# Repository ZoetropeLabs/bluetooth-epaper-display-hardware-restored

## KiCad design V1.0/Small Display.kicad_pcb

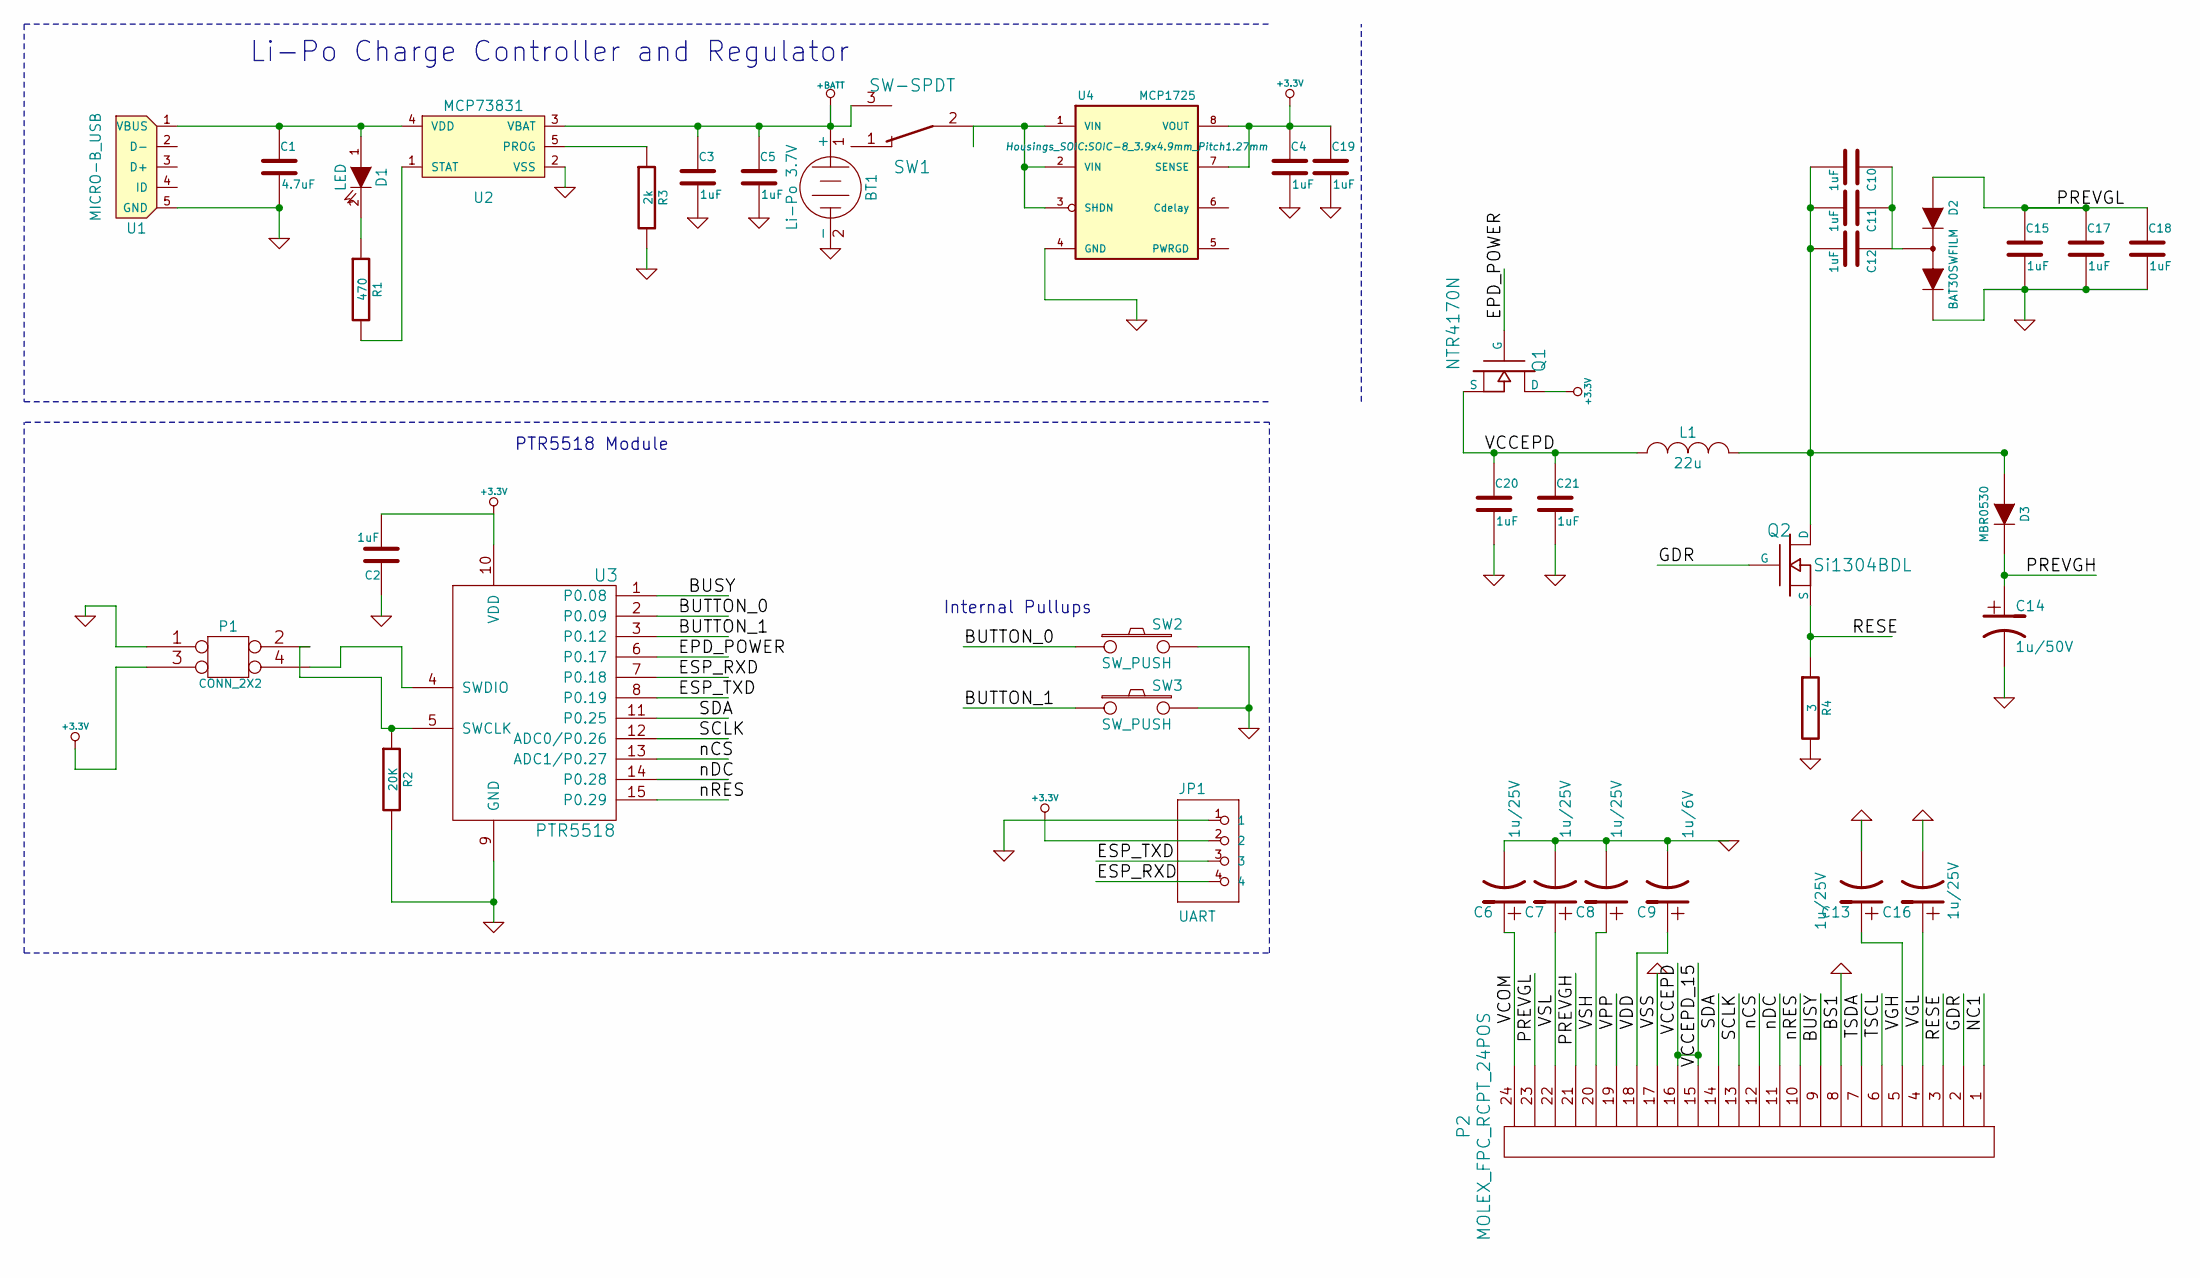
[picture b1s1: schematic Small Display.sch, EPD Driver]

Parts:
BT1: Li-Po 3.7V; Pin_Header_Straight_1x02
C1: 4.7uF; TantalC_SizeC_EIA-6032_Reflow
C2, C10, C11, C12, C15, C17, C18: 1uF; C_0603
C3, C4, C19, C20, C21: 1uF; TantalC_SizeC_EIA-6032_Reflow
C5: 1uF
C6, C7, C8, C13, C16: 1u/25V; C_0603
C9: 1u/6V; C_0603
C14: 1u/50V; C_0603
D1: LED; LED-0603
D2: BAT30SWFILM; SOT-323
D3: MBR0530; SOD-323
JP1: UART; Pin_Header_Straight_1x04
L1: 22u; R_1210_HandSoldering
P1: CONN_2X2; Pin_Header_Straight_2x02
P2: MOLEX_FPC_RCPT_24POS; MOLEX_FPC_RCPT_24POS_0_5MM
Q1: NTR4170N; SOT-23
Q2: Si1304BDL; SOT-323
R1: 470; R_0603
R2: 20K; R_0603
R3: 2k; R_0603
R4: 3; R_0603
SW1: SW-SPDT; SW_Micro_SPST
SW2, SW3: SW_PUSH; SW_M6_COMBO
U1: MICRO-B_USB; conn_usb_B_micro_smd
U2: MCP73831; SOT-23-5
U3: PTR5518
U4: MCP1725; SOIC-8_3.9x4.9mm_Pitch1.27mm

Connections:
+BATT: BT1.1 (+), C3.1, C5.1, SW1.3, U2.3 (VBAT)
/BUSY: P2.9, U3.1 (P0.08)
/BUTTON_0: SW2.1, U3.2 (P0.09)
/BUTTON_1: SW3.1, U3.3 (P0.12)
/EPD_POWER: Q1.1 (G), U3.6 (P0.17)
/ESP_RXD: JP1.4, U3.7 (P0.18)
/ESP_TXD: JP1.3, U3.8 (P0.19)
/GDR: P2.2, Q2.1 (G)
/NC1: P2.1
/PREVGH: C14.1, D3.2 (K), P2.21
/PREVGL: C15.1, C17.1, C18.1, D2.1 (A), P2.23
/RESE: P2.3, Q2.2 (S), R4.1
/SCLK: P2.13, U3.12 (ADC0/P0.26)
/SDA: P2.14, U3.11 (P0.25)
/TSCL: P2.6
/TSDA: P2.7
/VCCEPD: C20.1, C21.1, L1.1, P2.15, P2.16, Q1.2 (S)
/VCOM: C6.1, P2.24
/VDD: C9.1, P2.18
/VGH: C13.1, P2.5
/VGL: C16.1, P2.4
/VPP: P2.19
/VSH: C8.1, P2.20
/VSL: C7.1, P2.22
/nCS: P2.12, U3.13 (ADC1/P0.27)
/nDC: P2.11, U3.14 (P0.28)
/nRES: P2.10, U3.15 (P0.29)
unnamed: C1.1, D1.1 (A), U1.1 (VBUS), U2.4 (VDD)
unnamed: C10.1, C11.1, C12.1, D2.3 (Com)
unnamed: C10.2, C11.2, C12.2, D3.1 (A), L1.2, Q2.3 (D)
unnamed: D1.2 (K), R1.1
unnamed: P1.2, R2.1, U3.5 (SWCLK)
unnamed: P1.4, U3.4 (SWDIO)
unnamed: R1.2, U2.1 (STAT)
unnamed: R3.1, U2.5 (PROG)
unnamed: SW1.2, U4.1 (VIN), U4.2 (VIN), U4.3 (SHDN)

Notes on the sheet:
Li-Po Charge Controller and Regulator
PTR5518 Module
Internal Pullups

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
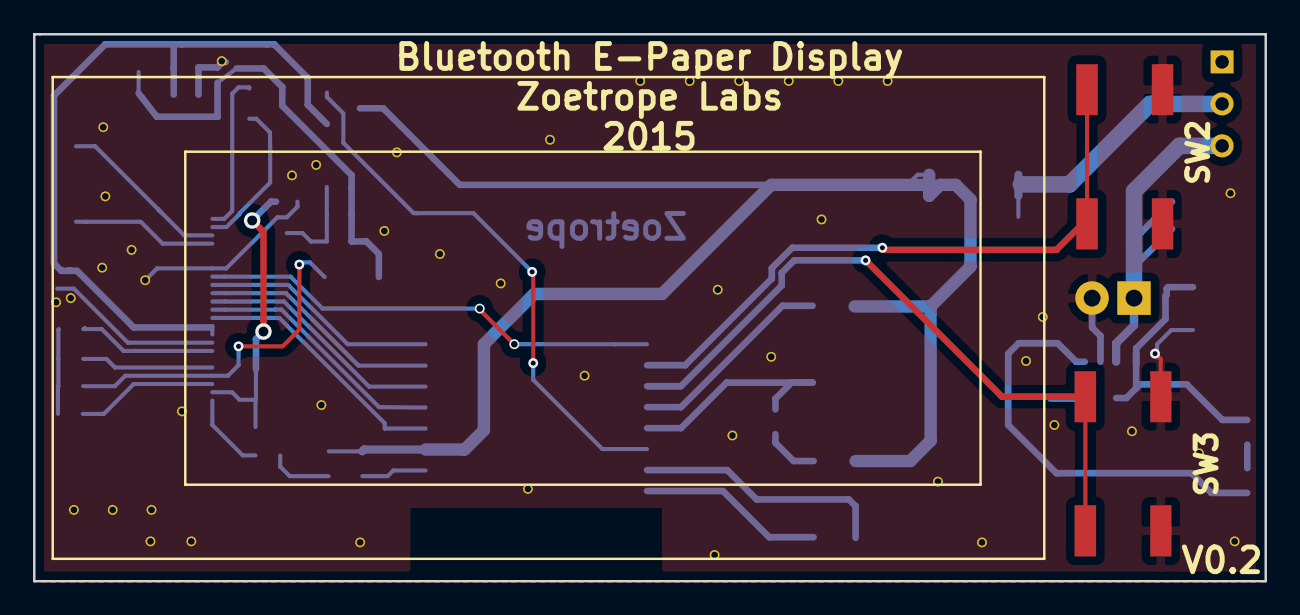
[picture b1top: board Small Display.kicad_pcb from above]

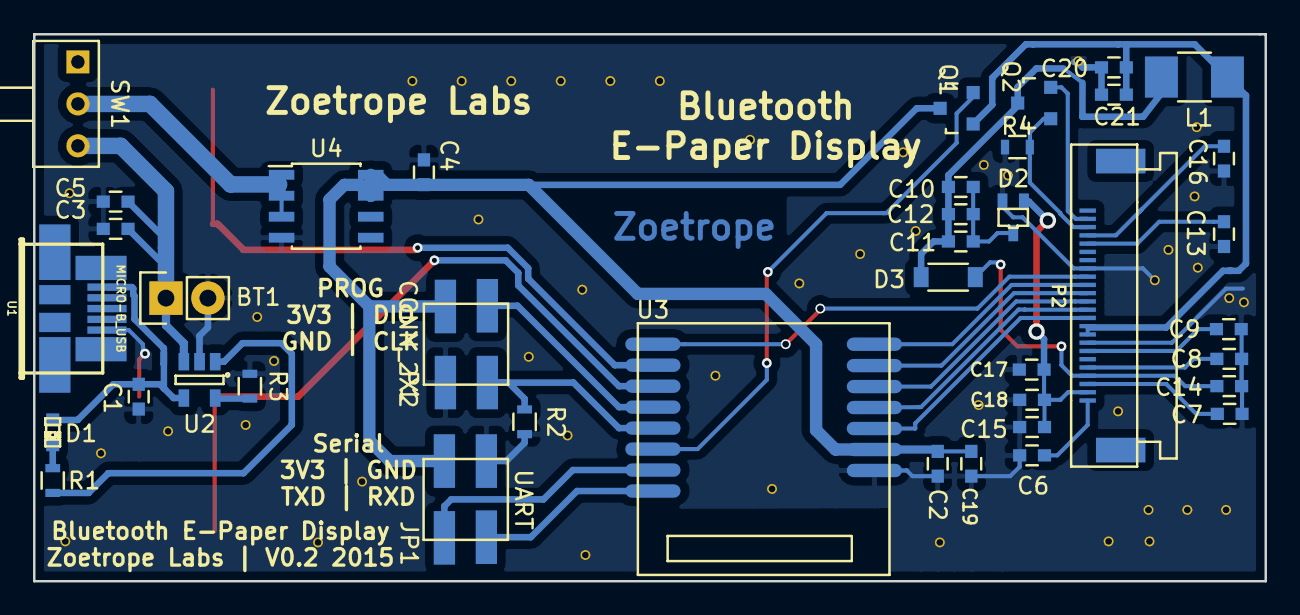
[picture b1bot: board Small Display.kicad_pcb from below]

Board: 2 copper layers, 74.6 x 33.1 mm, 42 parts (40 on the bottom side), 34 nets.

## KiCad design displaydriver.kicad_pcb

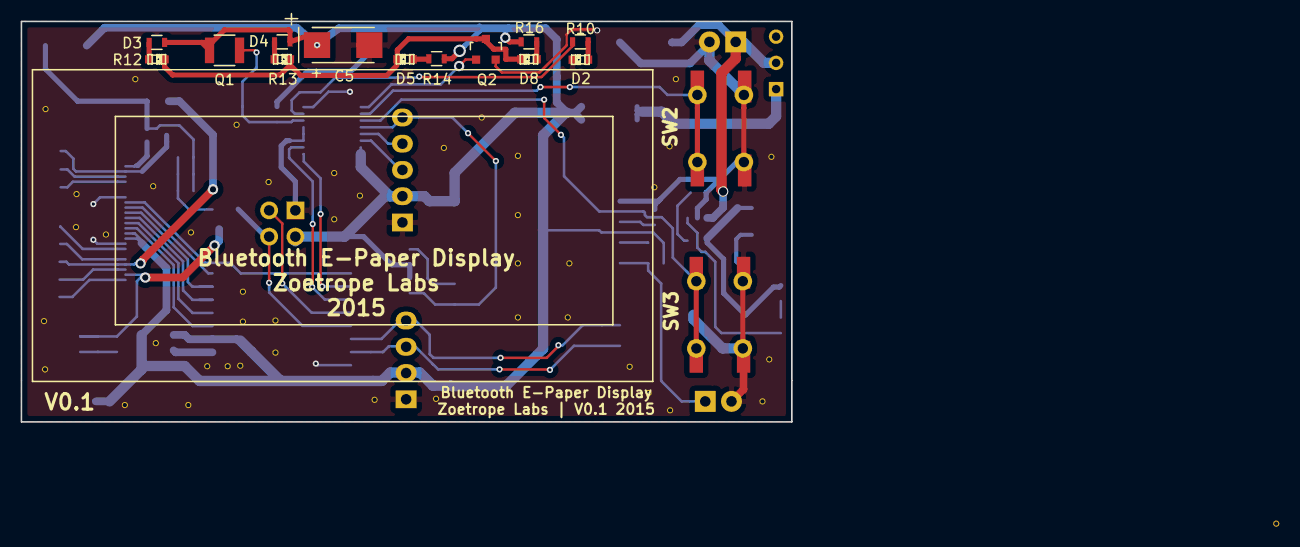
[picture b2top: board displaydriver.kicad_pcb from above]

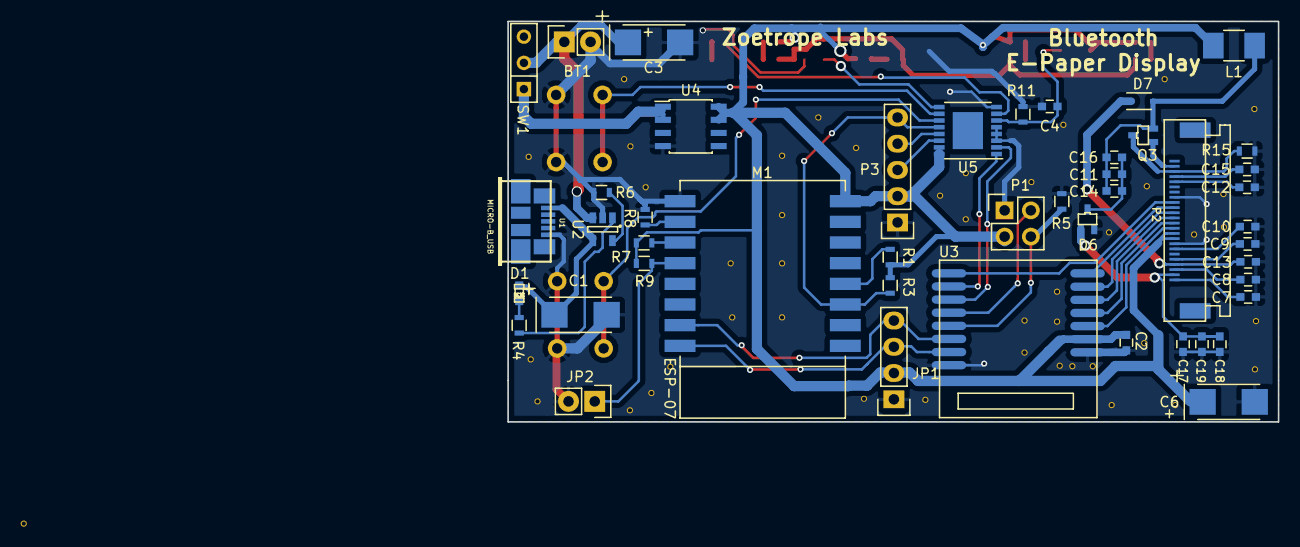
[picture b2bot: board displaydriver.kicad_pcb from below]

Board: 2 copper layers, 74.6 x 38.8 mm, 109 parts (46 on the bottom side), 50 nets.

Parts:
BT1: Li-Po 3.7V; Pin_Header_Straight_1x02
C1, C3, C5: 4.7uF; TantalC_SizeC_EIA-6032_Reflow
C2, C4: C; C_0603
C6: 4u7/6V; TantalC_SizeC_EIA-6032_Reflow
C7, C8, C9, C12, C15: 1u/25V; C_0603
C10: 1u/6V; C_0603
C11, C14, C16, C17, C18, C19: 1uF; C_0603
C13: 1u/50V; C_0603
D1, D2, D3, D4, D5, D8: LED; LED-0603
D6: BAT30SWFILM; SOT-323
D7: MBR0530; SOD-323
GND2, GND3, GND6, GND7, GND8, GND9, GND10, GND14, GND15, GND16, GND17, GND18, GND19, GND20, GND22, GND23, GND24, GND25, GND25#2, GND26, GND27, GND28, GND29, GND30, GND31, GND32, GND33, GND34, GND41, GND41#2, GND42, GND42#2, GND43, GND44, GND45, GND46, GND46#2, GND46#3, GND47, GND48, GND48#2, GND48#3, GND49, GND51, GND52, GND61, GND410, GND411: GND; VIA_0.6_0.4
JP1: UART; Pin_Header_Straight_1x04
JP2: JUMPER; Pin_Header_Straight_1x02
L1: 22u; R_1210_HandSoldering
M1: ESP-07
P1: CONN_2X2; Pin_Header_Straight_2x02
P2: MOLEX_FPC_RCPT_24POS; MOLEX_FPC_RCPT_24POS_0_5MM
P3: CONN_5; Pin_Header_Straight_1x05
Q1: PHOTO-TRANSISTOR-NPN; R_1210
Q2: NTR4170N; SOT-23
Q3: Si1304BDL; SOT-323
R1, R3, R7, R8, R9: 10K; R_0603
R4, R6, R10, R11, R12, R13, R14, R16: R; R_0603
R5: 20K; R_0603
R15: 3R; R_0603
SW1: SW-SPDT; SW_Micro_SPST
SW2, SW3: SW_PUSH; SW_M6_COMBO
U1: MICRO-B_USB; conn_usb_B_micro_smd
U2: MCP73831; SOT-23-5
U3: PTR5518
U4: MCP1725; SOIC-8_3.9x4.9mm_Pitch1.27mm
U5: PCA9557PWR; TSSOP-16-1EP_4.4x5mm_Pitch0.65mm

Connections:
+3.3V: C2.2, C5.1, C6.1, JP1.2, L1.1, M1.8, P1.3, P2.15, P2.16, P3.2, Q1.1, R1.1, R3.1, R7.2, R9.2, R12.1, R13.1, R14.1, R16.1, U3.10, U4.7, U4.8, U5.15, U5.16
+BATT: BT1.1, C3.1, SW1.2, U2.3
/BACKLIGHT: Q2.1, U5.9
/BUSY: P2.9, U3.1
/BUTTON_0: SW2.1, U5.10
/BUTTON_1: SW3.1, U5.11
/ESP_CH_PD: M1.3, P3.5, R3.2, U5.12
/ESP_RXD: JP1.4, M1.15, U3.6
/ESP_TXD: JP1.3, M1.16, U3.7
/GDR: P2.2, Q3.1
/IO_SCL: U3.2, U5.1
/IO_SDA: U3.3, U5.2
/NOTIF_LED: R10.2, U5.7
/PREVGH: C13.1, D7.2, P2.21
/PREVGL: C17.1, C18.1, C19.1, D6.1, P2.23
/RESE: P2.3, Q3.3, R15.1
/SCLK: P2.13, U3.12
/SDA: P2.14, U3.11
/VCOM: C7.1, P2.24
/VDD: C10.1, P2.18
/VGH: C12.1, P2.5
/VGL: C15.1, P2.4
/VSH: C9.1, P2.20
/VSL: C8.1, P2.22
/nCS: P2.12, U3.13
/nDC: P2.11, U3.14
/nRES: P2.10, U3.15
GND: BT1.2, C1.2, C2.1, C3.2, C4.2, C5.2, C6.2, C7.2, C8.2, C9.2, C10.2, C12.2, C13.2, C15.2, C17.2, C18.2, C19.2, D2.2, D6.2, GND2.2, GND3.2, GND6.2, GND7.2, GND8.2, GND9.2, GND10.2, GND14.2, GND15.2, GND16.2, GND17.2, GND18.2, GND19.2, GND20.2, GND22.2, GND23.2, GND24.2, GND25.2, GND25#2.2, GND26.2, GND27.2, GND28.2, GND29.2, GND30.2, GND31.2, GND32.2, GND33.2, GND41.2, GND41#2.2, GND42.2, GND43.2, GND44.2, GND45.2, GND46.2, GND46#2.2, GND46#3.2, GND47.2, GND48.2, GND48#2.2, GND48#3.2, GND49.2, GND51.2, GND410.2, GND411.2, JP1.1, JP2.2, M1.9, P1.1, P2.8, P2.17, P3.1, Q2.2, R5.2, R6.2, R8.1, R11.2, R15.2, SW2.2, SW3.2, U1.5, U2.2, U3.8, U3.9, U4.4, U5.3, U5.4, U5.5, U5.8
unnamed: C1.1, D1.1, U1.1, U2.4
unnamed: C4.1, Q1.2, R11.1, U5.6
unnamed: C11.1, C14.1, C16.1, D6.3
unnamed: C11.2, C14.2, C16.2, D7.1, L1.2, Q3.2
unnamed: D1.2, R4.1
unnamed: D2.1, R10.1
unnamed: D3.1, R12.2
unnamed: D3.2, D4.2, D5.2, D8.2, Q2.3
unnamed: D4.1, R13.2
unnamed: D5.1, R14.2
unnamed: D8.1, R16.2
unnamed: JP2.1, M1.12, R9.1
unnamed: M1.4, R1.2
unnamed: M1.10, R8.2
unnamed: M1.11, R7.1
unnamed: P1.2, U3.4
unnamed: P1.4, R5.1, U3.5
unnamed: P3.3, U5.14
unnamed: P3.4, U5.13
unnamed: R4.2, U2.1
unnamed: R6.1, U2.5
unnamed: SW1.1, U4.1, U4.2

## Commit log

2015-06-26 Initial Commit, still need to add more caps
2015-08-24 Add FS files
